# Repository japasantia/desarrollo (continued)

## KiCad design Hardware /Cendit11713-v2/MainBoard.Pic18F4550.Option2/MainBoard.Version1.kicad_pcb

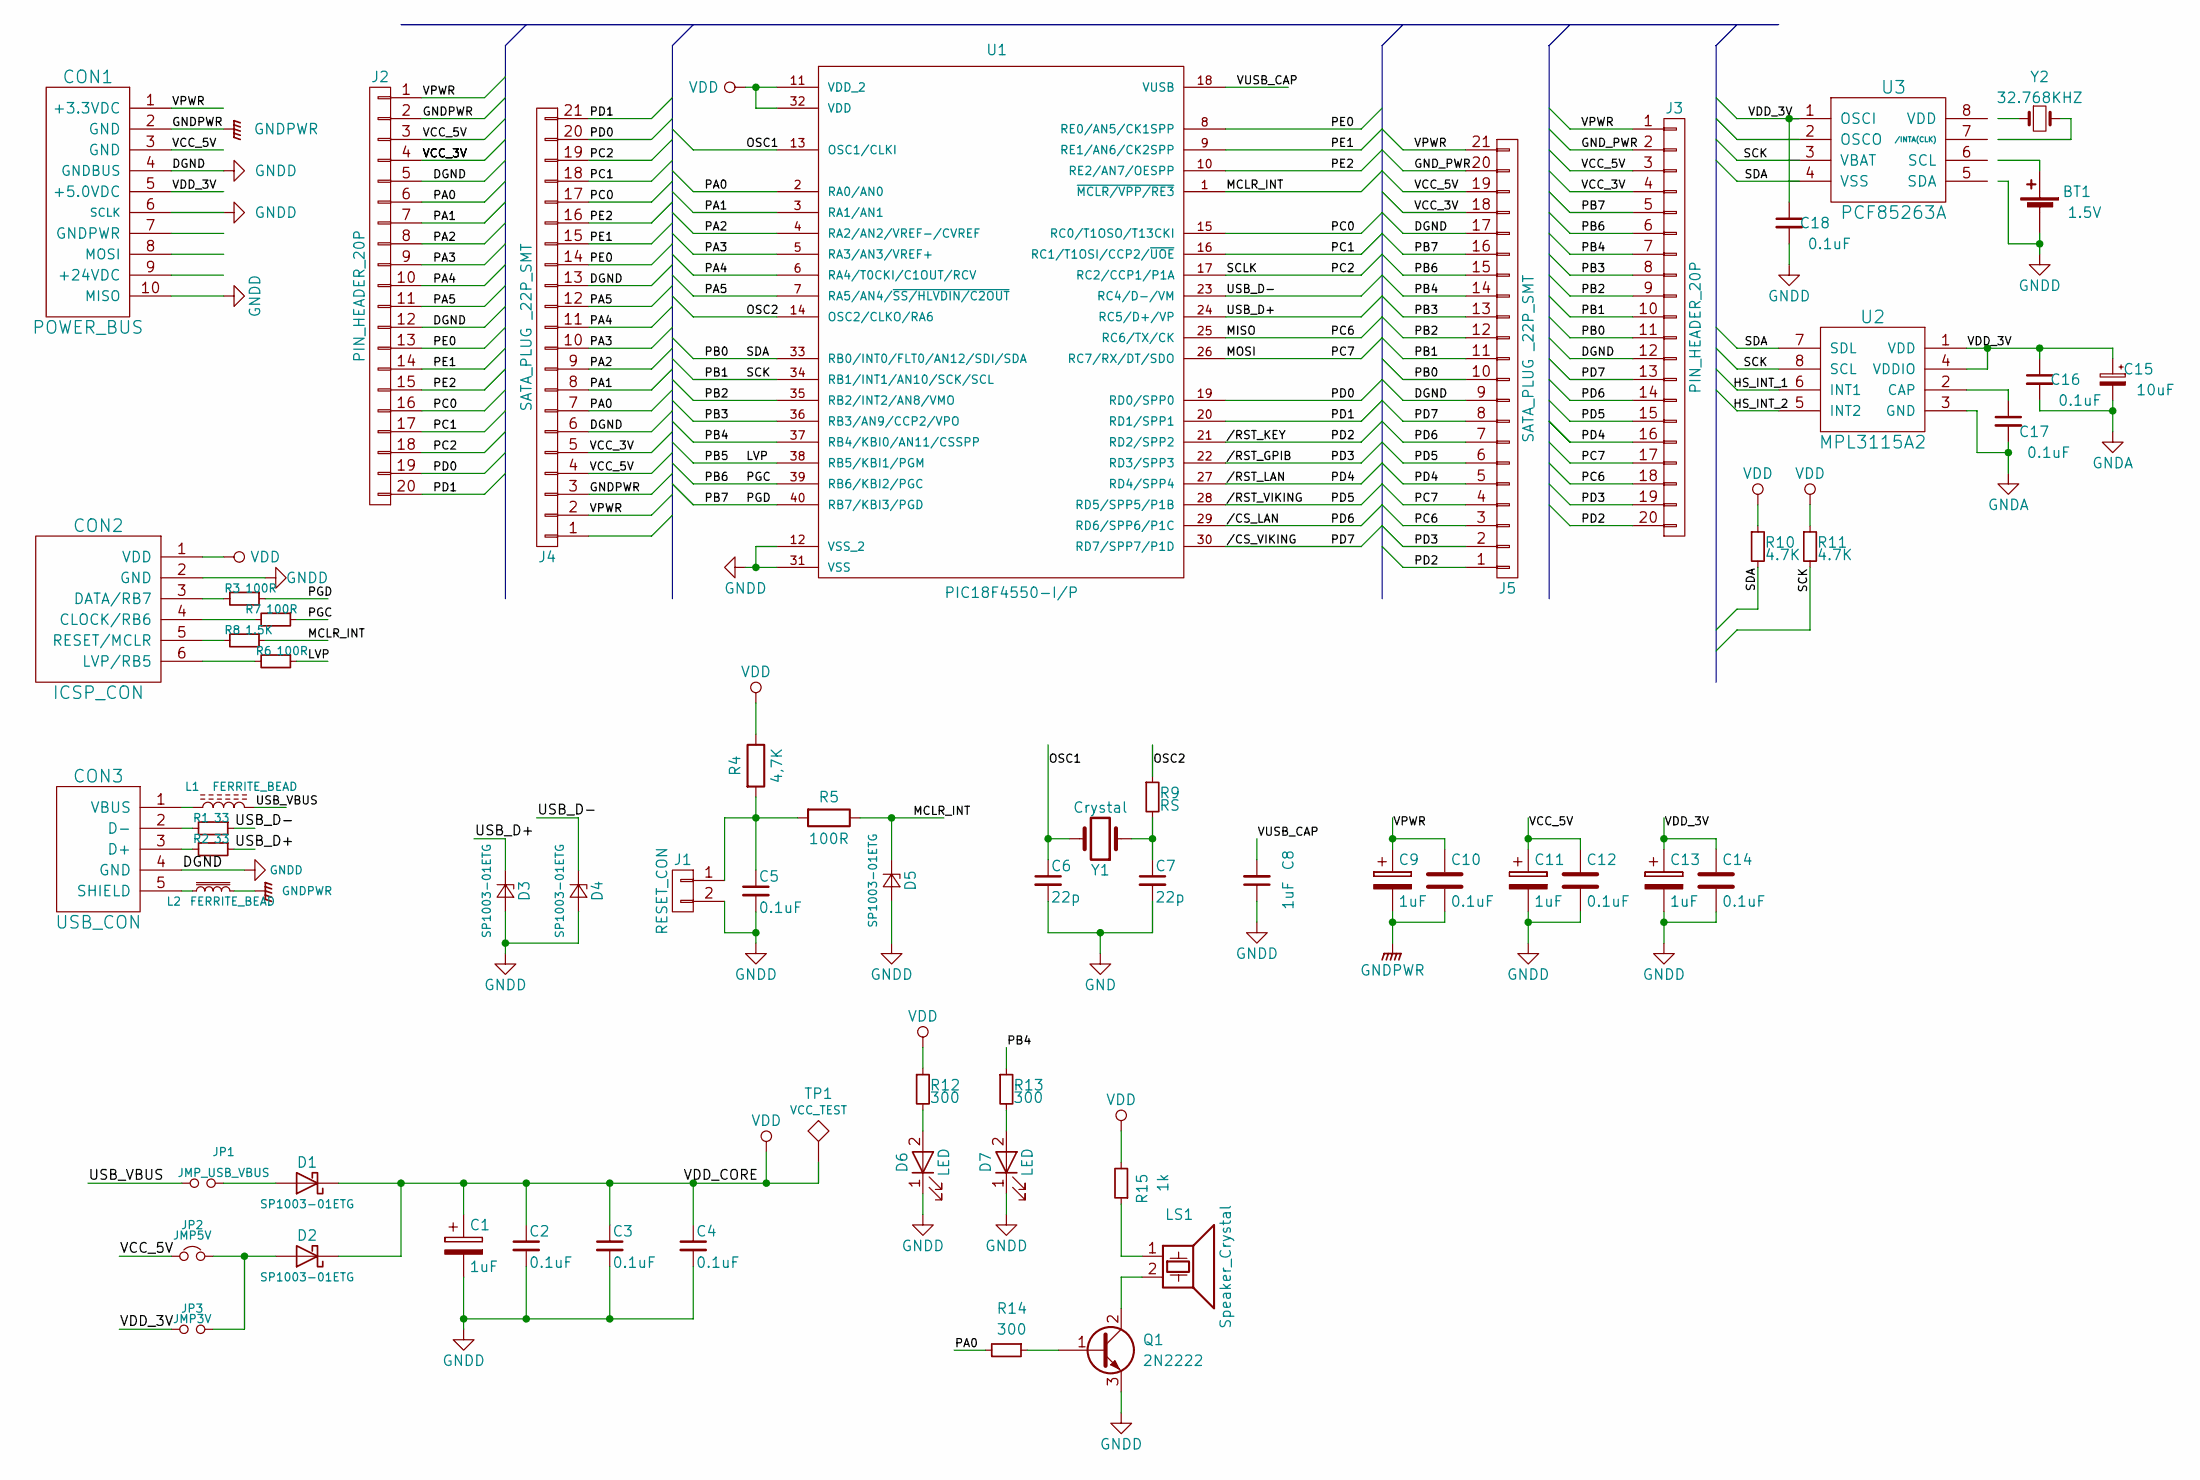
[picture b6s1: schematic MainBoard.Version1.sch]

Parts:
BT1: 1.5V
C1, C8, C9, C11, C13: 1uF; C_1206_HandSoldering
C2, C3, C4, C5, C10, C12, C14, C16, C17, C18: 0.1uF; C_0805_HandSoldering
C6, C7: 22p; C_0805_HandSoldering
C15: 10uF; C_1206_HandSoldering
CON1: POWER_BUS; Pin_Header_Straight_2x05
CON2: ICSP_CON; Pin_Header_Straight_2x03
CON3: USB_CON; USB_SMT_B
D1, D2, D3, D4, D5: SP1003-01ETG
D6, D7: LED; LED_0805
J1: RESET_CON; Pin_Header_Straight_1x02_Pitch2.54mm
J2, J3: PIN_HEADER_20P; Pin_Header_Straight_1x20_Pitch2.54mm
J4, J5: SATA_PLUG _22P_SMT; SATA_PLUG_22P_SMT
JP1: JMP_USB_VBUS; Pin_Header_Straight_1x02_Pitch2.54mm
JP2: JMP5V; Pin_Header_Straight_1x02_Pitch2.54mm
JP3: JMP3V; Pin_Header_Straight_1x02_Pitch2.54mm
L1, L2: FERRITE_BEAD; L_Axial_L5.3mm_D2.2mm_P2.54mm_Vertical_Vishay_IM-1
LS1: Speaker_Crystal; MagneticBuzzer_Kingstate_KCG0601
Q1: 2N2222; TSOT-23
R1, R2: 33; R_0603_HandSoldering
R3, R5, R6, R7: 100R; R_0805_HandSoldering
R4: 4,7K; R_0805_HandSoldering
R8: 1.5K; R_0805_HandSoldering
R9: RS; R_0805_HandSoldering
R10, R11: 4.7K; R_0805_HandSoldering
R12, R13, R14: 300; R_0805_HandSoldering
R15: 1k; R_0805_HandSoldering
TP1: VCC_TEST
U1: PIC18F4550-I/P; DIP254P1524X635-40
U2: MPL3115A2
U3: PCF85263A; PCF85263A_SO8
Y1: Crystal; Crystal_HC49-4H_Vertical
Y2: 32.768KHZ; Crystal_C26-LF_d2.1mm_l6.5mm_Vertical

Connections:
//CS_LAN: J3.14, J5.7, U1.29 (RD6/SPP6/P1C)
//CS_VIKING: J3.13, J5.8, U1.30 (RD7/SPP7/P1D)
//RST_GPIB: J3.19, J5.2, U1.22 (RD3/SPP3)
//RST_KEY: J3.20, J5.1, U1.21 (RD2/SPP2)
//RST_LAN: J3.16, J5.5, U1.27 (RD4/SPP4)
//RST_VIKING: J3.15, J5.6, U1.28 (RD5/SPP5/P1B)
/GND_PWR: J3.2, J5.20
/LVP: R6.1, U1.38 (RB5/KBI1/PGM)
/MCLR_INT: D5.1 (K), R5.1, R8.1, U1.1 (~MCLR/VPP/RE3)
/MISO: J3.18, J5.3, U1.25 (RC6/TX/CK)
/MOSI: J3.17, J5.4, U1.26 (RC7/RX/DT/SDO)
/OSC1: C6.1, U1.13 (OSC1/CLKI), Y1.2
/OSC2: R9.1, U1.14 (OSC2/CLKO/RA6)
/PA0: J2.6, J4.7, R14.2, U1.2 (RA0/AN0)
/PA1: J2.7, J4.8, U1.3 (RA1/AN1)
/PA2: J2.8, J4.9, U1.4 (RA2/AN2/VREF-/CVREF)
/PA3: J2.9, J4.10, U1.5 (RA3/AN3/VREF+)
/PA4: J2.10, J4.11, U1.6 (RA4/T0CKI/C1OUT/RCV)
/PA5: J2.11, J4.12, U1.7 (RA5/AN4/~SS/HLVDIN/C2OUT)
/PB0: J3.11, J5.10, R10.2, U1.33 (RB0/INT0/FLT0/AN12/SDI/SDA), U2.7 (SDL), U3.5 (SDA)
/PB1: J3.10, J5.11, R11.2, U1.34 (RB1/INT1/AN10/SCK/SCL), U2.8 (SCL), U3.6 (SCL)
/PB2: J3.9, J5.12, U1.35 (RB2/INT2/AN8/VMO)
/PB3: J3.8, J5.13, U1.36 (RB3/AN9/CCP2/VPO)
/PB4: J3.7, J5.14, R13.1, U1.37 (RB4/KBI0/AN11/CSSPP)
/PB6: J3.6, J5.15, R7.1, U1.39 (RB6/KBI2/PGC)
/PB7: J3.5, J5.16, R3.1, U1.40 (RB7/KBI3/PGD)
/PC0: J2.16, J4.17, U1.15 (RC0/T1OSO/T13CKI)
/PC1: J2.17, J4.18, U1.16 (RC1/T1OSI/CCP2/~UOE)
/PC2: J2.18, J4.19, U1.17 (RC2/CCP1/P1A)
/PD0: J2.19, J4.20, U1.19 (RD0/SPP0)
/PD1: J2.20, J4.21, U1.20 (RD1/SPP1)
/PE0: J2.13, J4.14, U1.8 (RE0/AN5/CK1SPP)
/PE1: J2.14, J4.15, U1.9 (RE1/AN6/CK2SPP)
/PE2: J2.15, J4.16, U1.10 (RE2/AN7/OESPP)
/USB_D+: D3.1 (K), R2.1, U1.24 (RC5/D+/VP)
/USB_D-: D4.1 (K), R1.1, U1.23 (RC4/D-/VM)
/USB_VBUS: JP1.1, L1.2
/VCC_3V: J2.4, J3.4, J4.5, J5.18
/VCC_5V: C11.1, C12.1, CON1.3 (GND), J2.3, J3.3, J4.4, J5.19, JP2.1
/VPWR: C9.1, C10.1, CON1.1 (+3.3VDC), J2.1, J3.1, J4.2, J5.21
/VUSB_CAP: C8.2, U1.18 (VUSB)
GND: C6.2, C7.2
GNDA: C15.2, C16.2, C17.2, U2.3 (GND)
GNDD: BT1.2 (-), C1.2, C2.2, C3.2, C4.2, C5.2, C8.1, C11.2, C12.2, C13.2, C14.2, C18.2, CON1.4 (GNDBUS), CON1.6 (SCLK), CON1.10 (MISO), CON2.2 (GND), CON3.4 (GND), D3.2 (A), D4.2 (A), D5.2 (A), D6.1 (K), D7.1 (K), J1.2, J2.5, J2.12, J3.12, J4.6, J4.13, J5.9, J5.17, Q1.3 (E), U1.12 (VSS_2), U1.31 (VSS), U3.4 (VSS)
GNDPWR: C9.2, C10.2, CON1.2 (GND), J2.2, J4.3, L2.2
unnamed: C5.1, J1.1, R4.2, R5.2
unnamed: C7.1, R9.2, Y1.1
unnamed: C17.1, U2.2 (CAP)
unnamed: CON2.3 (DATA/RB7), R3.2
unnamed: CON2.4 (CLOCK/RB6), R7.2
unnamed: CON2.5 (RESET/MCLR), R8.2
unnamed: CON2.6 (LVP/RB5), R6.2
unnamed: CON3.1 (VBUS), L1.1
unnamed: CON3.2 (D-), R1.2
unnamed: CON3.3 (D+), R2.2
unnamed: CON3.5 (SHIELD), L2.1
unnamed: D1.2 (A), JP1.2
unnamed: D2.2 (A), JP2.2, JP3.2
unnamed: D6.2 (A), R12.2
unnamed: D7.2 (A), R13.2
unnamed: LS1.1, R15.1
unnamed: LS1.2, Q1.2 (C)
unnamed: Q1.1 (B), R14.1
unnamed: U3.2 (OSCO), Y2.2
VDD: C1.1, C2.1, C3.1, C4.1, CON2.1 (VDD), D1.1 (K), D2.1 (K), R4.1, R10.1, R11.1, R12.1, R15.2, TP1.1, U1.11 (VDD_2), U1.32 (VDD)

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
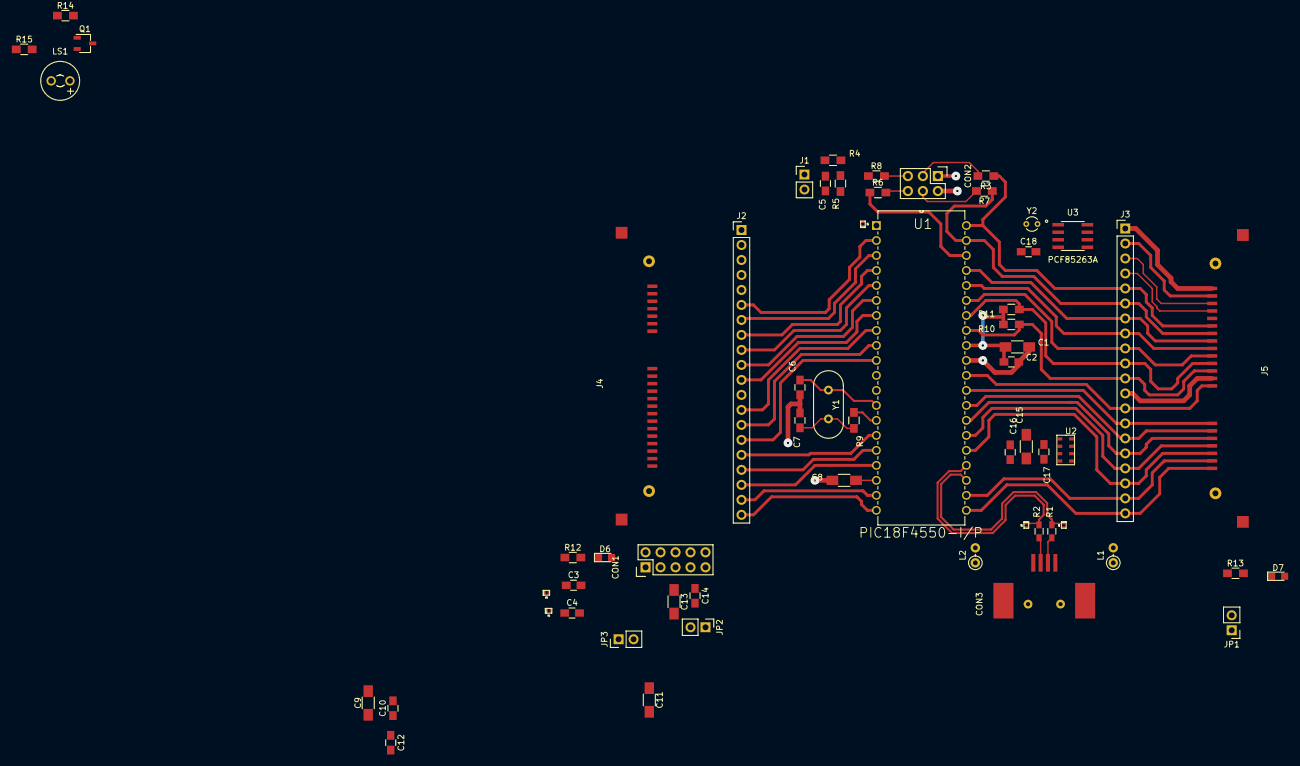
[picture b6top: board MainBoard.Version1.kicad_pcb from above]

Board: 2 copper layers, 60 parts (0 on the bottom side), 67 nets.

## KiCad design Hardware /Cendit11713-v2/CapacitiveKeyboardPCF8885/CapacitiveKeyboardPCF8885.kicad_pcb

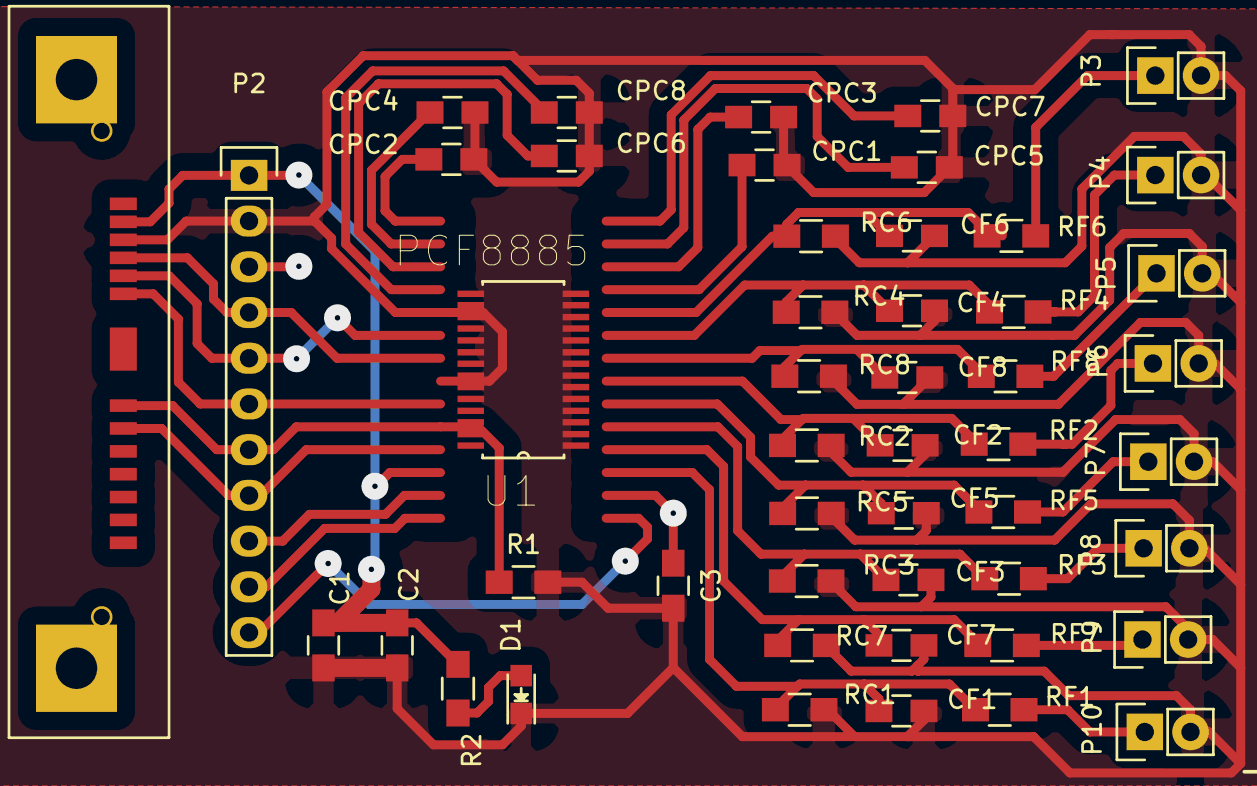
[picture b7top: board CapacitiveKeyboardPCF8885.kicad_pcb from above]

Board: 2 copper layers, 49 parts (0 on the bottom side), 36 nets.

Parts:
C1: 1uF; C_0805_HandSoldering
C2, C3: 100nF; C_0805_HandSoldering
CF1, CF2, CF3, CF4, CF5, CF6, CF7, CF8: 10p; C_0805_HandSoldering
CPC1, CPC2, CPC3, CPC4, CPC5, CPC6, CPC7, CPC8: 100nF; C_0805_HandSoldering
D1: LED; LED_0805
J1: I2C_CONN_01X13; SLIMLINE_SATA_PLUG_7P_6P
P2: DEBUG_CONN_01X11; Pin_Header_Straight_1x11
P3, P4, P5, P6, P7, P8, P9, P10: PLATE_CONN; Pin_Header_Straight_1x02
R1: 1OK; R_0805_HandSoldering
R2: 330; R_0805_HandSoldering
RC1, RC2, RC3, RC4, RC5, RC6, RC7, RC8: 10k; R_0805_HandSoldering
RF1, RF2, RF3, RF4, RF5, RF6, RF7, RF8: 5k; R_0805_HandSoldering
U1: PCF8885; PCF8885TS

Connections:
+3V3: C1.1, C2.1, J1.2, P2.1, R2.1, U1.26
//INT: J1.8, P2.8, U1.25
//INT_IN: P2.9, U1.27
/A0: J1.6, P2.6, U1.23
/CLK_IN: P2.10, U1.28
/CLK_OUT: P2.11, U1.1
/IN0: CF6.1, RC6.1, RF6.2, U1.10
/IN1: CF4.1, RC4.1, RF4.2, U1.9
/IN2: CF8.1, RC8.1, RF8.2, U1.8
/IN3: CF2.1, RC2.1, RF2.2, U1.7
/IN4: CF5.1, RC5.1, RF5.2, U1.6
/IN5: CF3.1, RC3.1, RF3.2, U1.5
/IN6: CF7.1, RC7.1, RF7.2, U1.4
/IN7: CF1.1, RC1.1, RF1.2, U1.3
/PLATE0: P3.1, RF6.1
/PLATE1: P4.1, RF4.1
/PLATE2: P5.1, RF8.1
/PLATE3: P6.1, RF2.1
/PLATE4: P7.1, RF5.1
/PLATE5: P8.1, RF3.1
/PLATE6: P9.1, RF7.1
/PLATE7: P10.1, RF1.1
/SCL: J1.5, P2.5, U1.20
/SDA: J1.4, P2.4, U1.21
/SLEEP: J1.7, P2.7, R1.1, U1.24
GNDA: C1.2, C2.2, C3.2, CF1.2, CF2.2, CF3.2, CF4.2, CF5.2, CF6.2, CF7.2, CF8.2, CPC1.1, CPC2.1, CPC3.1, CPC4.1, CPC5.1, CPC6.1, CPC7.1, CPC8.1, D1.1, J1.3, P2.2, P3.2, P4.2, P5.2, P6.2, P7.2, P8.2, P9.2, P10.2, R1.2, RC1.2, RC2.2, RC3.2, RC4.2, RC5.2, RC6.2, RC7.2, RC8.2, U1.19, U1.22
unnamed: CPC1.2, U1.11
unnamed: CPC2.2, U1.15
unnamed: CPC3.2, U1.12
unnamed: CPC4.2, U1.16
unnamed: CPC5.2, U1.13
unnamed: CPC6.2, U1.17
unnamed: CPC7.2, U1.14
unnamed: CPC8.2, U1.18
unnamed: D1.2, R2.2
VDD: C3.1, P2.3, U1.2

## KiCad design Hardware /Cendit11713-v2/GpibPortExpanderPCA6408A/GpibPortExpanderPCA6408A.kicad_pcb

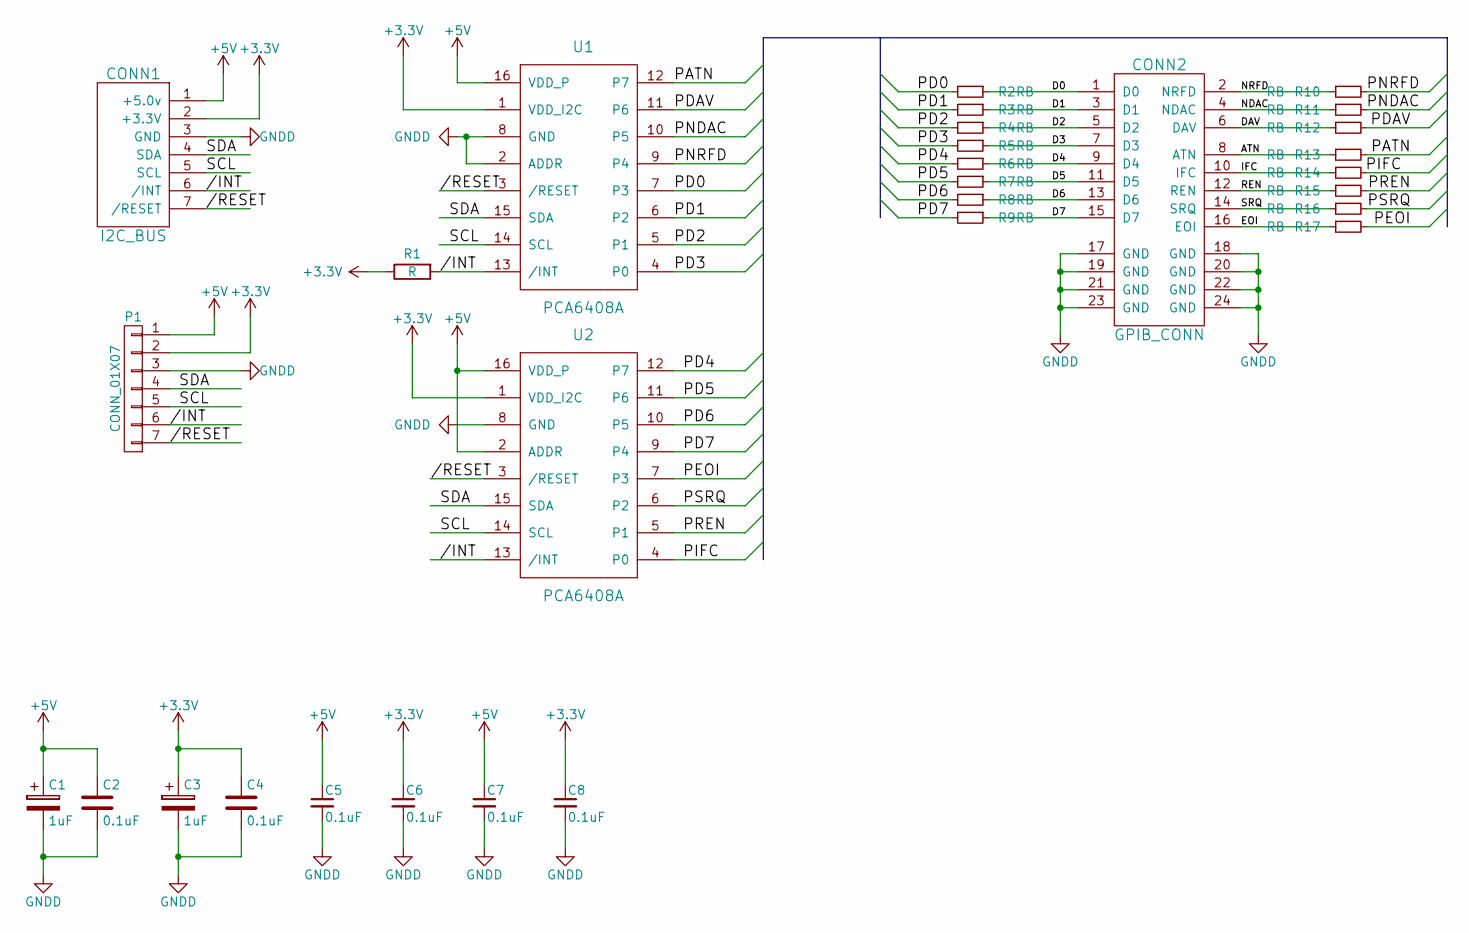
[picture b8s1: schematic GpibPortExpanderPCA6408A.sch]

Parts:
C1, C3: 1uF; C_1206_HandSoldering
C2, C4, C5, C6, C7, C8: 0.1uF; C_0805_HandSoldering
CONN1: I2C_BUS; SLIMLINE_SATA_PLUG_7P_6P
CONN2: GPIB_CONN; GPIB_HEADER_12X2P
P1: CONN_01X07; Pin_Header_Straight_1x07
R1: R; R_0805_HandSoldering
R2, R3, R4, R5, R6, R7, R8, R9, R10, R11, R12, R13, R14, R15, R16, R17: RB; R_0805_HandSoldering
U1, U2: PCA6408A; PCA6408A-SOP16

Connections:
+3V3: C3.1, C4.1, C6.1, C8.1, CONN1.2 (+3.3V), P1.2, R1.1, U1.1 (VDD_I2C), U2.1 (VDD_I2C)
//INT: CONN1.6 (/INT), P1.6, R1.2, U1.13 (/INT), U2.13 (/INT)
//RESET: CONN1.7 (/RESET), P1.7, U1.3 (/RESET), U2.3 (/RESET)
/ATN: CONN2.8 (ATN), R13.1
/D0: CONN2.1 (D0), R2.1
/D1: CONN2.3 (D1), R3.1
/D2: CONN2.5 (D2), R4.1
/D3: CONN2.7 (D3), R5.1
/D4: CONN2.9 (D4), R6.1
/D5: CONN2.11 (D5), R7.1
/D6: CONN2.13 (D6), R8.1
/D7: CONN2.15 (D7), R9.1
/DAV: CONN2.6 (DAV), R12.1
/EOI: CONN2.16 (EOI), R17.1
/IFC: CONN2.10 (IFC), R14.1
/NDAC: CONN2.4 (NDAC), R11.1
/NRFD: CONN2.2 (NRFD), R10.1
/PATN: R13.2, U1.12 (P7)
/PD0: R2.2, U1.7 (P3)
/PD1: R3.2, U1.6 (P2)
/PD2: R4.2, U1.5 (P1)
/PD3: R5.2, U1.4 (P0)
/PD4: R6.2, U2.12 (P7)
/PD5: R7.2, U2.11 (P6)
/PD6: R8.2, U2.10 (P5)
/PD7: R9.2, U2.9 (P4)
/PDAV: R12.2, U1.11 (P6)
/PEOI: R17.2, U2.7 (P3)
/PIFC: R14.2, U2.4 (P0)
/PNDAC: R11.2, U1.10 (P5)
/PNRFD: R10.2, U1.9 (P4)
/PREN: R15.2, U2.5 (P1)
/PSRQ: R16.2, U2.6 (P2)
/REN: CONN2.12 (REN), R15.1
/SCL: CONN1.5 (SCL), P1.5, U1.14 (SCL), U2.14 (SCL)
/SDA: CONN1.4 (SDA), P1.4, U1.15 (SDA), U2.15 (SDA)
/SRQ: CONN2.14 (SRQ), R16.1

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
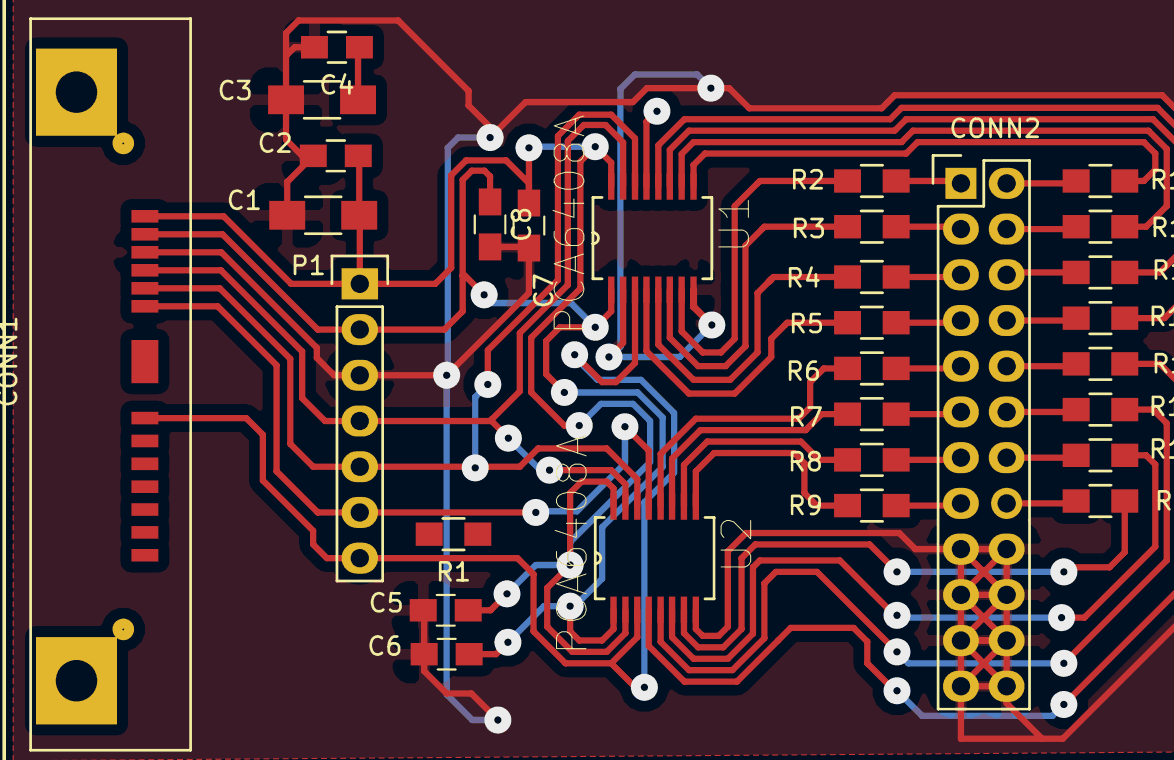
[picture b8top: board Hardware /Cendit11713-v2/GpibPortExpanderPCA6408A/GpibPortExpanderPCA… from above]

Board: 2 copper layers, 30 parts (0 on the bottom side), 39 nets.

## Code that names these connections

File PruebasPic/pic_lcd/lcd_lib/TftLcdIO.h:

#ifndef TFT_LCD_IO_H
#define TFT_LCD_IO_H

// #include "Arduino.h"
#include "TftLcdDef.h"

#define INLINE inline

#define CS_PORT     PORTC
#define RST_PORT    PORTC
#define RD_PORT     PORTC
#define WR_PORT     PORTA

#define YP_BIT      WR_BIT
#define YM_BIT      PORTBbits.RB7
#define XP_BIT      PORTBbits.RB6
#define XM_BIT      CD_BIT

#define YP_TRIS_BIT      TRISAbits.RA1
#define YM_TRIS_BIT      TRISBbits.RB7
#define XP_TRIS_BIT      TRISBbits.RB6
#define XM_TRIS_BIT      TRISAbits.RA0

#define CS_BIT      PORTCbits.RC1
#define RST_BIT     PORTCbits.RC2
#define RD_BIT      PORTCbits.RC0
#define WR_BIT      PORTAbits.RA1
#define CD_BIT      PORTAbits.RA0

#define LOW         0
#define HIGH        1


/*
void setControlIdle();
void setRstIdle();
void setCsIdle();
void setRsIdle();
void setWrIdle();
void setRdIdle();
*/

int TftLcdIO_Init();

void TftLcdIO_SetControlIdle();

INLINE void TftLcdIO_SetCsActive();

INLINE void TftLcdIO_SetWrActive();

INLINE void TftLcdIO_SetRdActive();

INLINE void TftLcdIO_SetCdActive();

INLINE void TftLcdIO_SetRstActive();

INLINE void TftLcdIO_SetCsIdle();

INLINE void TftLcdIO_SetWrIdle();

INLINE void TftLcdIO_SetRdIdle();

INLINE void TftLcdIO_SetCdIdle();

INLINE void TftLcdIO_SetRstIdle();

INLINE void TftLcdIO_SetCdCommand();

INLINE void TftLcdIO_SetCdData();

void TftLcdIO_SetWriteDir();

void TftLcdIO_SetReadDir();

INLINE void TftLcdIO_WrStrobe();

INLINE void TftLcdIO_Write8(byte d);

byte TftLcdIO_Read8();

void TftLcdIO_WriteRegister8(byte a, byte d);

void TftLcdIO_WriteRegister16(int a, int d);

void TftLcdIO_WriteRegister24(uint8_t r, uint32_t d);

void TftLcdIO_WriteRegister32(byte r, long int d);
/*
#define writeRegisterPairInline(aH, aL, d) { \
uint8_t hi = (d) >> 8, lo = (d); \
CD_COMMAND; write8(aH); CD_DATA; write8(hi); \
CD_COMMAND; write8(aL); CD_DATA; write8(lo); }
*/
void TftLcdIO_WriteRegisterPair(uint8_t aH, uint8_t aL, uint16_t d);

void TftLcdIO_BeginTouchScreenRead();
void TftLcdIO_EndTouchScreenRead();

INLINE void TftLcdIO_HiImpedanceXp();
INLINE void TftLcdIO_HiImpedanceXm();
INLINE void TftLcdIO_HiImpedanceYp();
INLINE void TftLcdIO_HiImpedanceYm();

INLINE void TftLcdIO_OutputXp();
INLINE void TftLcdIO_OutputXm();
INLINE void TftLcdIO_OutputYp();
INLINE void TftLcdIO_OutputYm();

INLINE void TftLcdIO_SetXp();
INLINE void TftLcdIO_SetXm();
INLINE void TftLcdIO_SetYp();
INLINE void TftLcdIO_SetYm();

INLINE void TftLcdIO_ClrXp();
INLINE void TftLcdIO_ClrXm();
INLINE void TftLcdIO_ClrYp();
INLINE void TftLcdIO_ClrYm();

INLINE unsigned int TftLcdIO_AnalogReadYp();
INLINE unsigned int TftLcdIO_AnalogReadXm();

#endif

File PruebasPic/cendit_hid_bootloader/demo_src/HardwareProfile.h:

/*******************************************************************************
Copyright 2016 Microchip Technology Inc. (www.microchip.com)

Licensed under the Apache License, Version 2.0 (the "License");
you may not use this file except in compliance with the License.
You may obtain a copy of the License at

    http://www.apache.org/licenses/LICENSE-2.0

Unless required by applicable law or agreed to in writing, software
distributed under the License is distributed on an "AS IS" BASIS,
WITHOUT WARRANTIES OR CONDITIONS OF ANY KIND, either express or implied.
See the License for the specific language governing permissions and
limitations under the License.

To request to license the code under the MLA license (www.microchip.com/mla_license), 
please contact mla_licensing@microchip.com
*******************************************************************************/

#ifndef __HARDWARE_PROFILE_H_
#define __HARDWARE_PROFILE_H_


/** I N C L U D E S *************************************************/
#include "usb_config.h"


//Make sure board/platform specific definitions (like config bit settings and
//I/O pin definitions are correct for your hardware platform).
#if defined(__18F4550)
    #define PIC18F4550_PICDEM_FS_USB
#elif defined(__18F45K50)
    #define PIC18F4550_PICDEM_FS_USB_K50
#elif defined(__18F14K50)
    #define LOW_PIN_COUNT_USB_DEVELOPMENT_KIT
#else
    #define YOUR_CUSTOM_BOARD
    #warning "You need to add platform specific settings for your hardware.  Double click this message for more details."
    //In order to use a hardware platform other than a Microchip USB demo board, you need to make
    //sure the following are correctly configured for your hardware platform:
    //1. Configuration bit settings (especially the oscillator settings, which must be compatible with USB operation).
    //2. I/O pin definitions for VBUS sensing, self power sensing, I/O pushbutton for entry into bootloader, and for LED blink settings.
    //3. Optional behavioral settings: ENABLE_IO_PIN_CHECK_BOOTLOADER_ENTRY, ENABLE_USB_LED_BLINK_STATUS, USE_SELF_POWER_SENSE_IO, USE_USB_BUS_SENSE_IO.  See usb_config.h file.
    //4. Oscillator and other settings are correctly being initialized in the InitializeSystem() function, specific to your hardware (ex: turn on PLL [if needed] for proper USB clock, etc.)
#endif


#if defined(PIC18F4550_PICDEM_FS_USB)   //Based on PIC18F4550, for PIC18F45K50 based board, see farther below
    //VBUS sensing pin definition, applicable if using the USE_USB_BUS_SENSE_IO option in usb_config.
    #if defined(USE_USB_BUS_SENSE_IO)
        #define tris_usb_bus_sense  TRISAbits.TRISA1    // Input
        #define usb_bus_sense       PORTAbits.RA1
    #endif
    #if defined(USE_SELF_POWER_SENSE_IO)
        #define tris_self_power     TRISAbits.TRISA2
        #define self_power          PORTAbits.RA2
    #endif

    //LED definition, applicable if using ENABLE_USB_LED_BLINK_STATUS option in usb_config.h
    #define mLED1       LATDbits.LATD0
    #define mLED1Tris   TRISDbits.TRISD0
    /** SWITCH *********************************************************/
    /*
    #define mInitSwitch2()      {ADCON1 = 0x0F; TRISBbits.TRISB4 = 1;}   
    #define sw2                 PORTBbits.RB4
    #define mDeInitSwitch2()    {ADCON1 = 0x07;} 
    */
    // BEGIN MOD Jose Arias
    #define mInitSwitch2()      {ADCON0bits.ADON = 0; ADCON1 = 0x0F; CMCON = 0x07; TRISAbits.TRISA0 = 1; LATAbits.LATA0 = 1;}   
    #define sw2                 LATAbits.LATA0
    #define mDeInitSwitch2()    {ADCON1 = 0x07;} 
    // END MOD

#elif defined(PIC18F4550_PICDEM_FS_USB_K50)  //Section for PIC18F45K50 when on the PICDEM FS USB Demo Board
    //VBUS sensing pin definition, applicable if using the USE_USB_BUS_SENSE_IO option in usb_config.
    #if defined(USE_USB_BUS_SENSE_IO)
        #define tris_usb_bus_sense  TRISAbits.TRISA1    // Input
        #define usb_bus_sense       PORTAbits.RA1
    #endif
    #if defined(USE_SELF_POWER_SENSE_IO)
        #define tris_self_power     TRISAbits.TRISA2
        #define self_power          PORTAbits.RA2       
    #endif

    //LED definition, applicable if using ENABLE_USB_LED_BLINK_STATUS option in usb_config.h
    #define mLED1       LATDbits.LATD0
    #define mLED1Tris   TRISDbits.TRISD0
    /** SWITCH *********************************************************/
    #define mInitSwitch2()      {ANSELBbits.ANSB4 = 0; TRISBbits.TRISB4 = 1;}   
    #define sw2                 PORTBbits.RB4
    #define mDeInitSwitch2()    {ANSELBbits.ANSB4 = 1;} 



#elif defined(LOW_PIN_COUNT_USB_DEVELOPMENT_KIT)  //Based on PIC18F14K50
    //VBUS sensing pin definition, applicable if using the USE_USB_BUS_SENSE_IO option in usb_config.
    #if defined(USE_USB_BUS_SENSE_IO)
        #define tris_usb_bus_sense  TRISAbits.TRISA1    // Input
        #define usb_bus_sense       PORTAbits.RA1
    #endif
    #if defined(USE_SELF_POWER_SENSE_IO)
        #define tris_self_power     TRISXbits.TRISXX    //Replace with real value if your hardware supports this feature
        #define self_power          PORTXbits.RXX       //Replace with real value if your hardware supports this feature
    #endif

    //LED definition, applicable if using ENABLE_USB_LED_BLINK_STATUS option in usb_config.h
    #define mLED1       LATCbits.LATC0
    #define mLED1Tris   TRISCbits.TRISC0
    /** SWITCH *********************************************************/
    #define mInitSwitch2()      {}                      //No TRISA3 bit.  RA3 is input only on this device
    #define sw2                 PORTAbits.RA3           //Requires MCLR disabled to use RA3 as general purpose input
    #define mDeInitSwitch2()    {} 
	
	

#elif defined(YOUR_CUSTOM_BOARD)
    #warning "Add your hardware specific I/O pin mapping here."
    //Use one of the existing sections as a template for adding the proper
    //macro defintions appropriate for your hardware platform.

#else
    #error Not a supported board (yet), add I/O pin mapping in __FILE__, line __LINE__
#endif




/** T R I S *********************************************************/
#define INPUT_PIN           1
#define OUTPUT_PIN          0


#endif //__HARDWARE_PROFILE_H_

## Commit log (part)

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2017-05-26 Respaldo inicial en Desarrollo
    Se abre el repositorio (nuevamente)
2017-05-29 Commit de respaldo
    Se hace commit masivo para respaldo
2017-06-01 Commit respaldo
    - Trabajo en pruebas de librerias VISA
    - Proyectos desarrollo actualizados
2017-06-06 Pruebas para adaptar libreria <linux-gpib> a Java, por medio de JNA. Respaldo
2017-06-10 Commit para sincronizar repositorios y respaldo
    Se han hecho cambios en PC-casa que no ha sido enviados al repositorio remoto.
2017-06-14 Se modifica archivo de proyecto libreria GPIB en Java
    - Modificación en interfaz ILinuxGPIB
2017-06-15 Respaldo, cambio de nombre archivos
2017-06-16 Trabajo en CenditLab, proyecto Communications
    - Modificacion CommunicationAbstractionLayer
2017-06-19 Trabajo en CenditLab
    - Modificaciones en torno a VisaAddress
2017-06-19 Respaldo de archivo VisaAddress.java para resolver problema de sincronia de repos (rebase)
2017-06-20 Trabajo en CenditLab, Communications - VisaAddress - GpibConnection - Excepciones
2017-06-21 Modificaciones en CenditLab.Communications
    Trabajo en capa comunicaciones GPIB
    - GpibConnection
    - VisaAddress
2017-06-26 Modificacion libreria TFT LCD para PIC18
    - Modificacion módulo TftLcdIO para adaptarlo a los puertos de PIC18F4550
    - Definicion de pines
    - Modificacion de rutinas inicializacion
2017-06-29 Modificaciones en firmware PIC
    - Cendit HID bootloader: resuelto problema con boton booloader
    - Modificados algunos proyectos PIC18 USB
2017-06-29 Trabajo en Communications
    - Wrapper libreria VXI11
    - Prueba de conexion exitosa con VXI11
2017-06-30 Actualizacion de Communications en CenditLab
    - Agregados coentarios relativos a libreria VXI11
    - Trabajo en clase Vxi11Connection
2017-07-07 Trabajo en desarrollo: CenditLab + Pic
    - En CenditLab inicia desarrollo adaptadores Visa.
    - Modificaciones a proyecto PIC pic_lcd.
2017-07-11 Se agregan dos proyectos en desarrollo
    - Modificación del proyecto Cendit Hid Bootloader
    - Nuevo proyecto pic_serial_pc: consola serial para la tarjeta CenditBoard
2017-07-14 Trabajo en desarrollo: CenditLab
    - Continua desarrollo librearia Measurments, agregadas nuevas clases
    - Modificaciones en proyectos PIC
    - Se agregan proyectos prueba librerias de comunicacion serial
2017-07-17 Modificaciones en proyectos y limpieza directorios
    - Cambios en pic_lcd
    - Revision PicSerial
    - Revision cendit_hid_bootloader_pc
2017-07-18 Modificacion en proyecto pic_cd
    - Modificacion hecha para pruebas con libreria TFT LCD.
    - Respaldo de proyectos modificados anteriormente
2017-07-20 Modificacion en proyectos: pic_serial y pic_lcd
    - Cambios UI en pic_serial + nuevos comandos para probar libreria LCD
2017-07-20 Trabajo en CenditLab, replanteo de clases
    - Se replantea clase ScpiCommands, 3era prueba
2017-07-21 Modificaciones en CenditLab: Measurements y Communications
    - Se reimportan el proyectos, modificaciones en archivos proyecto, manifiestos.
    - Se refina ScpiCommand3
    - Modificadas clases relativas a Task, solo para poder compilar
2017-07-25 Trabajo en pic_lcd y PicSerial
    - Correcciones en libreria PIC LCD, ahora funciona
    - PicSerial utilidad para pruebas libreria PIC LCD, version inicial
2017-07-25 Se inicia proyecto pic_seial_32
    - Proyecto en Qt 5.2 32 bits.
2017-08-02 Commit respaldo
    - Libreria pic_lcd funcional
2017-08-15 Inicia desarrollo de CenditBoard, tarjeta reducida
2017-08-17 CenditLab, prueba nuevo concepto para organizar tareas y sus datos de in/out
    - Se idea un nuevo concepto para el manejo de datos de las tareas.
    - Clase Value, representa argumento de una tarea.
    - Nueva definicion de interfaz Task (Task2).
2017-08-18 Respaldo ultima hora
    - Proyecto Kicad tarjeta Cendit11713, v2
2017-08-23 Respaldo, trabajo en desarrollo de software+hardware
    - En hardware, tarjeta control puertos Viking (Shift register port exp)
    - En software edición ligera en CenditLab
2017-08-24 Trabajo en desarrollo CenditLab + hardware Cendit11713
    - Modulo Task, se crea clases para menejo de Instrumentos (Instrument)
    - Ediciones de esquematicos Cendit11714 + tarjeta Nokia 1600 LCD
2017-08-30 CenditLab, modulo Communications
    - Se importa modulo Communications
    - Proceso de revision y refactor de clases
    - Se crea instalador para pruebas, inicialmente instala modulo Views
2017-08-31 CenditLab, modulo Communications
    - Prosigue la revision de clases: Gpib + Vxi
    - Manejo de excepciones, creacion clase base CommunicationException
    - Pruebas exitosas
2017-09-05 CenditLab, trabajo GUI modulo Views + nuevos tipos de datos en Task
    - Se agregan vistas para arreglos (ArrayData)
    - Boton para barra de navegacion
    - Se agregan tipo de datos ArrayData en Tasks
2017-09-06 CenditLab, trabajo en Communications + Views
    - Comunications, revision + correcciones correspondientes a Vxi11
    - Views, modificaciones en ArrayDataView
2017-09-08 CenditLab, modulo Views + Tasks
    - En Views se agrega widget para graficos XY
    - En Tasks se corrigen fallas en clase ArrayData
2017-09-12 En CenditLab
    - Se modifica control GraphView para acoplarse con GraphData
    - Se renombran clases
    - Pruebas satisfactorias
2017-09-13 En CenditLab se trabaja en concepto para manejo de session de medicion
    - Se crean clases MeasurementSession y MeasurementStep
    - Pruebas con GUI y vistas
2017-09-14 Commit para respaldo ultima hora
2017-09-18 En CenditLab modificaciones en modulos Tasks + Views
    - Edicion de clases MeasurementSession y MeasurementStep
    - Creacion de objetos view StepsBarView y StepButtonView
    - Creacion de archivos fxml respectivos
2017-09-19 CenditLab + footprints PCB
    - En CenditLab se trabaja en UI Views, se crea ContainerWindow
    - Se realizan ajustes en StepButton y StepsBarView
    - Se crea footprint conector SATA
2017-09-21 CenditLab + esquematicos + PCB
    - En CenditLab creadas clases de vistas (Views)
    - Se crean footprints
2017-09-21 Commit adicional al anterior, respaldo
2017-09-27 CenditLab + Cendit11713 multiples cambios desarrollo software + hardware
    - CenditLab revision + reformulacion + refactor de clases
    - Cendit11713 creacion de footprints + esquematico controlador de teclado
2017-09-28 En CenditLab trabajo en modulo Views
    - Forma mas eficiente de generar vistas
    - Organizacion de vistas en filas y columnas
    - Clases RowContainerView + ColumnContainerView
2017-09-29 Trabajo en CenditLab
    - Clases para el organizacion de vistas en filas-columnas
2017-10-08 Trabajo en CenditLab.Reducido + Cendit11713
    - CenditLab componenets GUI setup frecuencia
    - Cendit11713 esquematicos expansor puerto GPIB
2017-10-09 En CenditLab.Reducido
    - Clases manejo de paneles y valores de frecuencia actualizados
2017-10-10 En CenditLab.Reducido
    - Modificacion y refactor de clases Field (FrequencyValue -> FrequencyField)
2017-10-10 Cendit11713: Trabajo en esquematicos + PCB
    - Se editan esquematicos expansor IO Viking
    - Creada tarjeta PCB adaptador multipuertos
2017-10-13 Trabajo en CenditLab.Reducido + Cendit17713 PCB
    - Clases paneles UI modificados
    - Clases para manejo y validacion de datos
    - PCB expansor puertos Viking
2017-10-16 Trabajo en CenditLab + Cendit11713 PCB
    - Clases UI entrada de ENR + archivos fxml
    - Expansor puertos Viking
    - Controlador teclado capacitivo
2017-10-17 Trabajo en CenditLab.Reducido + Cendit11713 PCB
    - CenditLab clases para manejo de setup ENR
    - Clase field para dato temperatura
    - Edición de PCBs Capacitive Keyboard
    - Edición de esquematico MainBoard con PIC18F4550 DIP
2017-10-19 Para Cendit11713 creacion de footprints
    - Interruptores luminosos
    - Sensor humedad SI70201
    - Sensor de presion MPL3115A2
2017-10-20 Cendit11713 respaldo del trabajo en PCBs
2017-10-20 En CendiLab edicion de archivo UI + Respaldo
    - Edicion de fxl para setup
    - Respaldo de archivos esquematicos + PCB
2017-10-22 CenditLab.Reducido respaldo de archivos
    - Archivos .java EnrSetup, FrequencySetup, TemperatureField
2017-10-24 En CenditLab.Reducido
    - Trabajo en clases FrequencySetup + FrequencySetupView.
    - Pruebas satisfactorias
2017-10-26 En CenditLab.Reducido + respaldo archivos Gerber
    - Se retoman clases de antiguo CenditLab
    - Clases relativas a MeasurementManager + MeasurementStep
    - Vista MeasurementBarView + StepButtonView
    - Se respaldan archivos Gerber
2017-10-27 En CenditLab.Reducido + Respaldo
    - Correccion de clase relativas a FieldsView (FieldInput + Field)
    - Respaldo de archivos Cendit11713 (esquematicos + PCB)
    - Respaldo diseño fuente: creado hoy
2017-10-31 En CenditLab: gestion de proceso de medicion en UI + pruebas
    - Clase que representa sistema-dispositivo NFA (System)
    - Clases que representan pasos de medicion (MeasurementStep)
    - Clases tareas asosciadas a NFA (Task)
2017-10-31 En CenditLab trabajo en vistas para setup
    - Clase SetupContainerView vista para configuracion
    - Nueva organizacion de modulos/directorios
    - Se debio reimportar proyectos
2017-11-01 En CenditLab.Reducido + Cendit11713
    - Clase para manejo setup frecuencia basico (BasicFrequencySetup)
    - Archivo fxml para esta clase
    - Correciones en FieldInput
    - Creada simulacion Multisim para high side driver
2017-11-02 Cendit11713 + aparecen modificadas clases Java
    - Diseño de high side driver simulacion Multisim
    - Aparecen modificadas clases Java BasicFrequencySetup, aunque no se hayan tocado
2017-11-02 En CenditLab.Reducido + Cendit11713
    - Clase para vista generica - contenedor top level (GenericMainView)
    - Simulación de un high side driver Multisim
2017-11-07 En CenditLab.Reducido + respaldo de esquematicos + PCBs
    - Clases vistas para cada paso de medicion
    - Respaldo de archivos Cendit11713 (esquematicos + PCBs)
2017-11-08 En CenditLab.Reducido + Cendit11713
    - Para CenditLab vistas para Steps + fabrica de vistas ComponentViewfactory
    - En Cendit11713 revision PCB VikingPortExpander + Gerber
2017-11-09 En CenditLab.Reducido + respaldo de Cendit11713
    - Clases fabrica de vistas ComponentViewFactory
    - Modificacion de clases MeasurementStep
    - Respaldo de archivos esquematicos + PCBs Cendit11713 (sin editar)
2017-11-10 Revision + correccion en CenditLab.Reducido + respaldo diseño hardware
    - Revisadas clases y archivos fxml + correcciones
    - No se modifican archivos hardware pero se respaldan
2017-11-10 En CenditLab.Reducido + Cendit11713
    - Hardware tarjeta madre opcion 2, esquematico + PCB
    - Software UI vistas de setup + steps
2017-11-13 En CenditLab.Reducido trabajo en clases UI
    - Diseño de clases + fxml UI para Tasks
    - Reorganizacion de directorio de recursos (imagenes + fxml)
    - Pruebas satisfactorias
2017-11-15 En CenditLab + Cendit11713
    - Diseño de clases UI para Steps (TaskExecutionStep)
    - Layout PCB tarjeta madre opcion 2
2017-11-16 En CenditLab correcciones en modulo UI
    - Para aumentar eficiencia
2017-11-22 En CenditLab + Cendit11713: commit masivo
    - Trabajo en clases + fxml UI
    - Trabajo en main board option 2 + correccion tarjeta expansor Viking
2017-11-22 Respaldo y continuacion comit anterior
2017-11-23 Trabajo en CenditLab + Cendit11713
    - Diseño + codigo UI
    - PCBs tarjeta madre + puertos Viking
    - Se generan Gerber para solicitud de prototipos PCB
2017-11-28 En Cendit11713 + respaldo de software
    - Esquematico tarjeta madre con PIC18F45K50
    - Respaldo de software CenditLab
    - Gerber files tarjeta interfaz GPIB
2017-11-29 Respaldo de CenditLab
    - Trabajo en UI
2017-11-30 En CenditLab + Cendit11713
    - Creados footprints de reguladores
    - Respaldo en CenditLab UI
2017-12-12 Respaldo de desarrollo
    - Trabajo en Cendit11713 esquematico exp puertos CD4094
2017-12-13 Cendit 11713 port expander CD4094 + respaldo
    - Inicia esquematico y PCB para IO expander con SR CD4094
    - Respaldo de software
